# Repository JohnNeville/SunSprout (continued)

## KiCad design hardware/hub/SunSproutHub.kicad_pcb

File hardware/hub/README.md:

# SunSproutHub — KiCad project

The hub board's KiCad 10 project. Open `SunSproutHub.kicad_pro`.

For the design reasoning behind each IC and its passives, see [docs/hub/modules/](../../docs/hub/modules/).

## Layout

| Path | Contents |
|---|---|
| `SunSproutHub.kicad_sch` | Root/hierarchical top sheet |
| `sheets/` | Hierarchical sub-sheets (charger, fuel gauge, regulator, user I2C) |
| `SunSproutHub.kicad_pcb` | Board layout, hand-routed |
| `SunSproutHub.kicad_dru` | Custom design rules |
| `../libraries/` | Project-specific and vendored symbol/footprint libraries (shared with Satellite) |
| `spice_models/` | ngspice decks used to verify the reverse-polarity FETs |

## Board revisions

The revision is set by the `REV_NUM` text variable in `SunSproutHub.kicad_pro`, which the
silkscreen prints alongside the commit hash. Change the title block revision in the PCB to match.

| Change | Bump | Example |
|---|---|---|
| Fixes and part changes that keep the same ICs and board dimensions | Minor | 1.0 → 1.1 |
| A change that replaces the main ICs or changes the board dimensions | Major | 1.x → 2.0 |

All Rev 1.x boards share the same outline, mounting holes and connector positions, so the
documentation refers to them as Rev 1.x. Rev 1.0 is the first prototype, built from commit
`1645733`.

## What you can do without any extra setup

KiCad writes the full geometry of every symbol and footprint directly into the
`.kicad_sch` and `.kicad_pcb` files at placement time. The schematic and the board are
therefore self-contained. After cloning you can open both, run ERC and DRC, inspect every
part, and export gerbers and a pick-and-place file, with no libraries beyond the ones KiCad
ships with.

## External library dependencies

**3D models are not external.** The board file carries an embedded copy of every 3D model
(KiCad's "Collect and Embed 3D Models"), so the board renders completely with nothing
installed.

Footprints are mostly in-repo too. Three library entries still resolve outside it, and they
are only consulted when you update a footprint *from its library* — not to open, review,
render, or fabricate the board, because the geometry is already in the board file.

| Library | Resolves via | Parts |
|---|---|---|
| `Snapeda` | `KICAD_3RD_PARTY` | `J201`, `J202`, `U3`, `U8`, `U4`, `U5`, `U201`, `D5`, `U202`, `Q301`-`Q304` |
| `PCM_JLCPCB` | PCM package ([CDFER](https://github.com/CDFER/JLCPCB-Kicad-Library), MIT) | The 0402 capacitors |
| `PCM_SparkFun-Connector` | PCM package | The test points |
| `PCM_Capacitor_SMD_AKL` | PCM package | `C17` only, which is DNP and not fitted |

If KiCad reports these as missing, the board is still correct. To silence the warnings,
install the matching PCM packages and point `KICAD_3RD_PARTY` at your own third-party library
directory, or remove the unused entries from `fp-lib-table`.

The `USBC1` USB-C footprint and the `CN5` screw terminal are project footprints, in
`../libraries/footprints/project.pretty/`. The Espressif module's footprint and 3D model are
vendored under `../libraries/vendor/`.

### A note on licensing

Every library this design still depends on has stated terms: SnapEDA is CC BY-SA 4.0 with the
Design Exception 1.0, CDFER's library is MIT, and Espressif's is CC BY-SA 4.0. All three are
credited in [NOTICE.md](../../NOTICE.md). Earlier revisions used EasyEDA/LCSC content, whose
redistribution terms are not published; it has since been replaced throughout and no longer
appears in the design or the embedded model set.

## Regenerating the documentation assets

The board renders, schematic PDF, STEP model, interactive BOM, and pinout SVG under
`website/static/` are all build artifacts of the files here. Regenerate them from the
repository root after any schematic or layout change:

```bash
tools/generate-docs-assets.sh
```

Docker is the only prerequisite. No local KiCad installation is required.

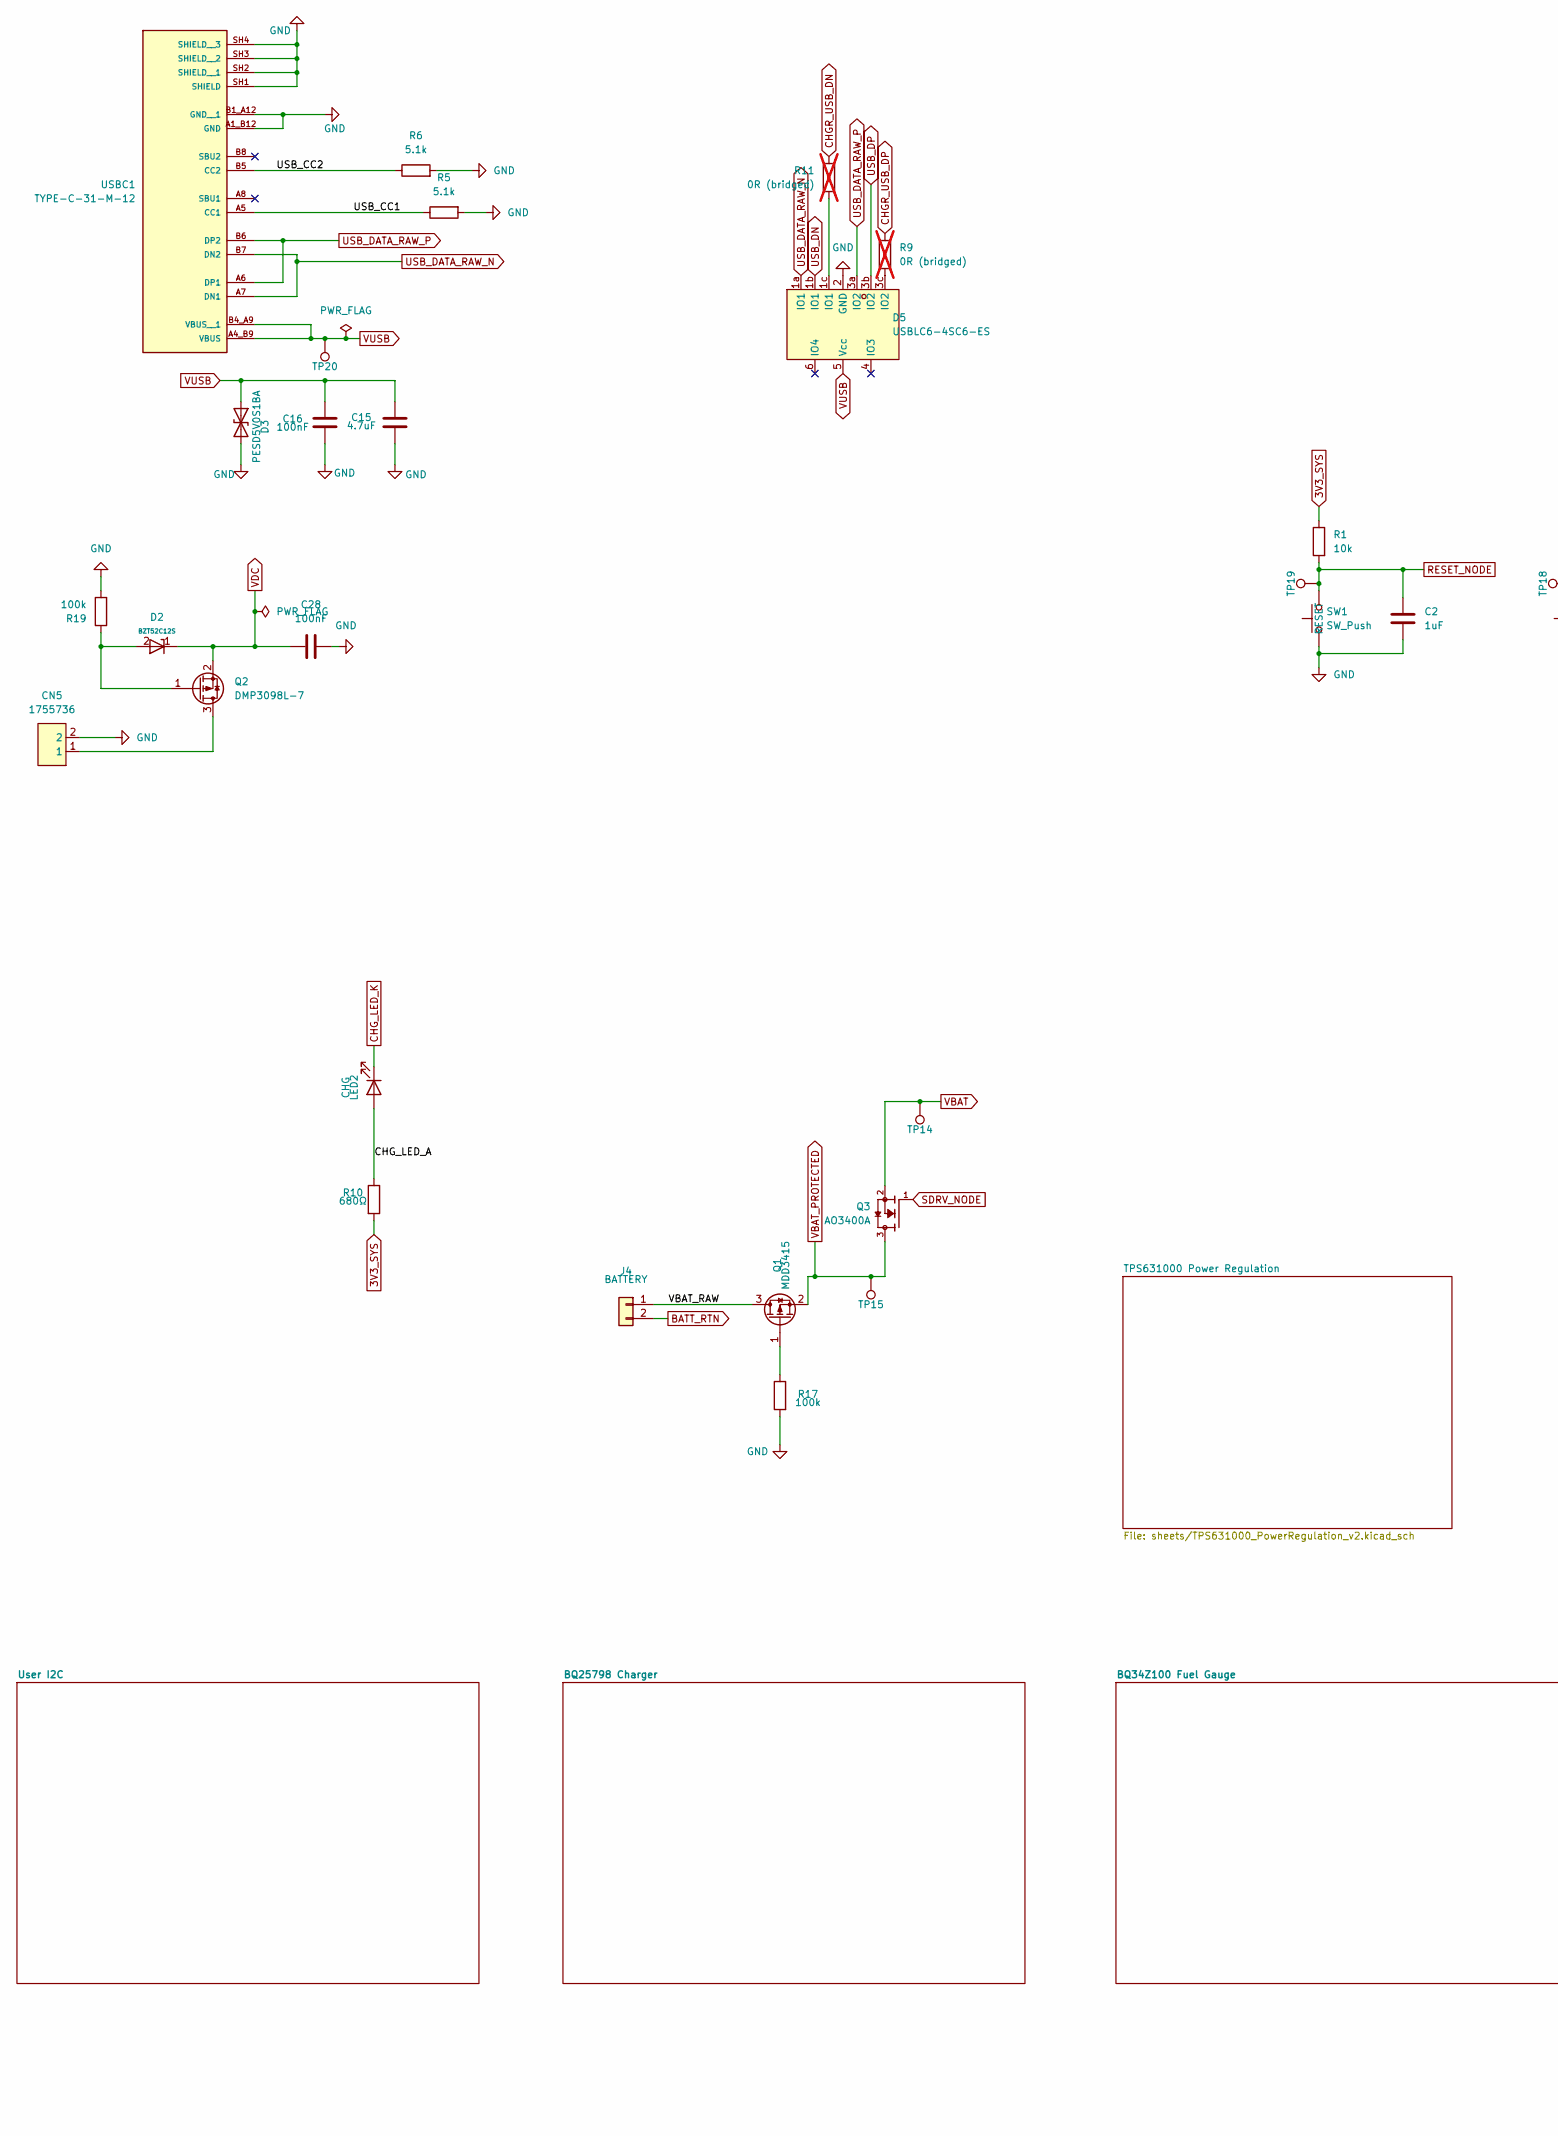
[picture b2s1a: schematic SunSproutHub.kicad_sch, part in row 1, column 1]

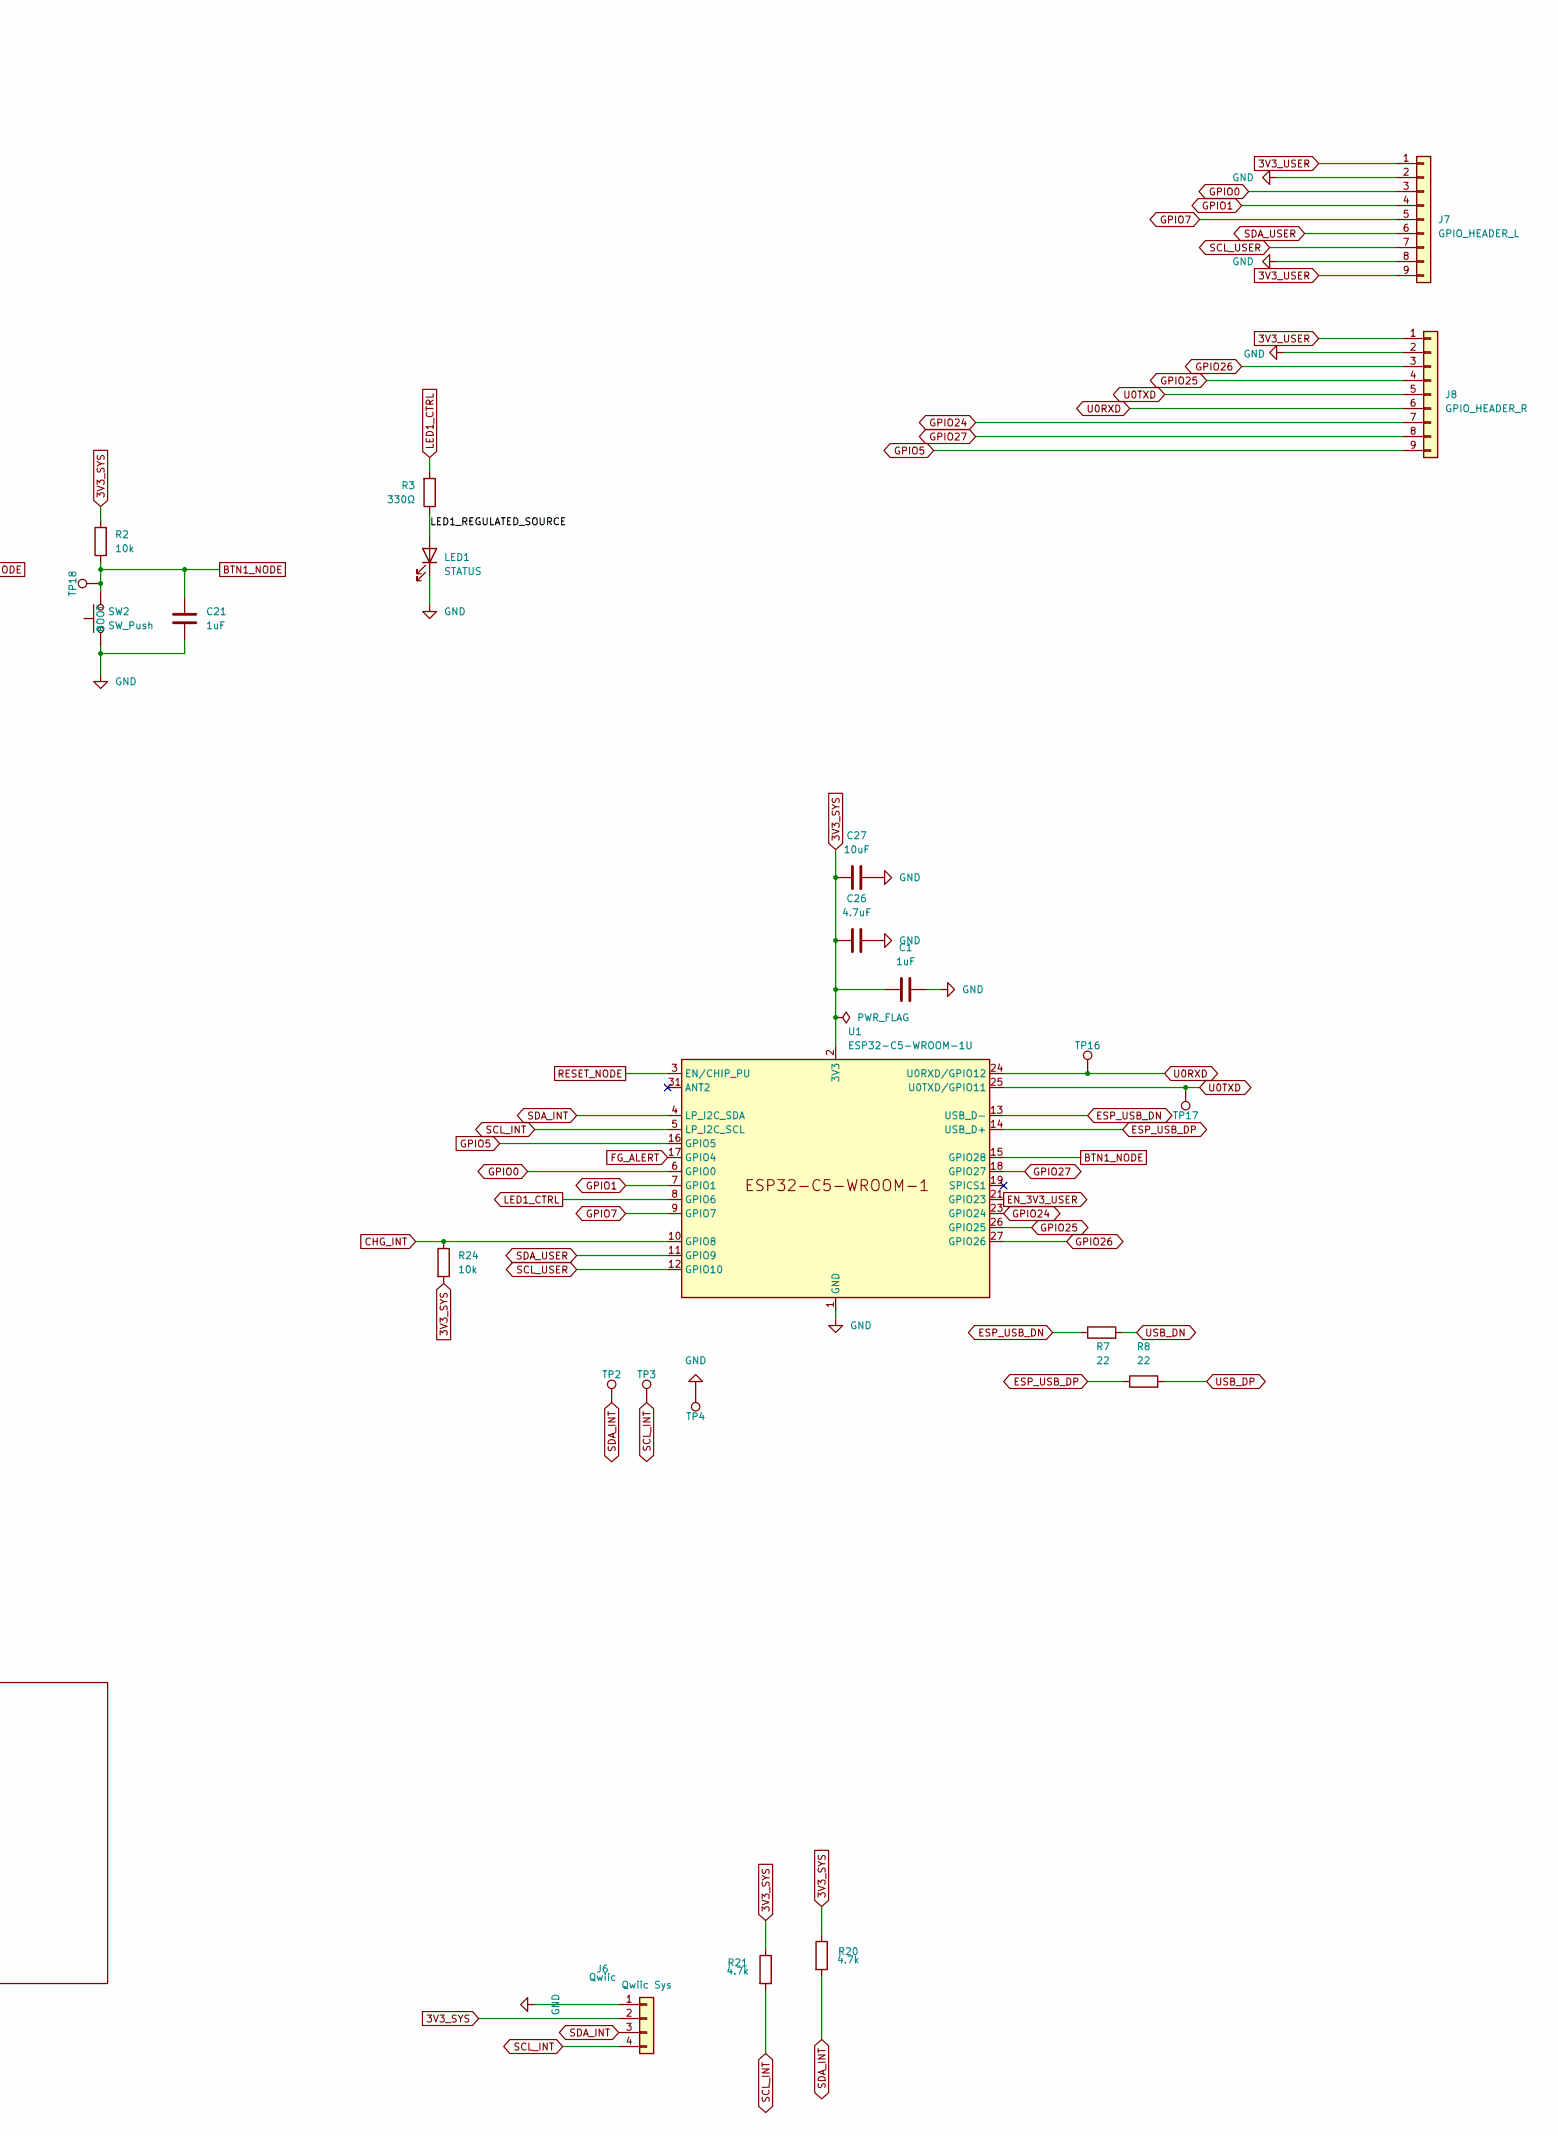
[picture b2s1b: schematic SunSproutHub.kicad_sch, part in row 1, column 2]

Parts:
C1, C2, C21: 1uF; C_0603_1608Metric; MPN CL10A105KB8NNNC; LCSC Part C15849
C15, C26: 4.7uF; C_0805_2012Metric; MPN CL21A475KAQNNNE; LCSC Part C1779
C16: 100nF; C_0402; MPN CL05B104KB54PNC; LCSC Part C307331
C27: 10uF; C_0603_1608Metric; MPN CL10A106MA8NRNC; LCSC Part C96446
C28: 100nF; C_0402; LCSC Part C307331
CN5: 1755736; DB125-2.54-2P-GN-S; MPN DB125-2.54-2P-GN-S; LCSC Part C918120
D2: BZT52C12S; D_SOD-323; MPN BZT52C12S; LCSC Part C19077447
D3: PESD5V0S1BA; D_SOD-523; LCSC Part C20615818
D5: USBLC6-4SC6-ES; USBLC6-4SC6-ES_WIthNetTie; MPN USBLC6-4SC6-ES; LCSC Part C5180279
J4: BATTERY; JST_PH_S2B-PH-K_1x02_P2.00mm_Horizontal; MPN S2B-PH-K(LF)(SN); LCSC Part C265016
J6: Qwiic; JST_SH_BM04B-SRSS-TB_1x04-1MP_P1.00mm_Vertical; MPN BM04B-SRSS-TB(LF)(SN); LCSC Part C160390
J7: GPIO_HEADER_L; LeftSide_PinHeader_1x09_P2.54mm_Vertical
J8: GPIO_HEADER_R; PinHeader_1x09_P2.54mm_Vertical
LED1: STATUS; LED_0603_1608Metric; MPN KT-0603W; LCSC Part C2290
LED2: CHG; LED_0603_1608Metric; MPN KT-0603R; LCSC Part C2286
Q1: MDD3415; SOT-23; MPN MDD3415; LCSC Part C840839
Q2: DMP3098L-7; SOT-23; MPN DMP3098L-7; LCSC Part C150492
Q3: AO3400A; SOT95P280X125-3N; MPN AO3400A; LCSC Part C20917
R1, R2, R24: 10k; R_0603_1608Metric; MPN 0603WAF1002T5E; LCSC Part C25804
R3: 330Ω; R_0603_1608Metric; MPN 0603WAF3300T5E; LCSC Part C23138
R5, R6: 5.1k; R_0603_1608Metric; MPN 0603WAF5101T5E; LCSC Part C23186
R7, R8: 22; R_0603_1608Metric; MPN 0603WAF220JT5E; LCSC Part C23345
R9, R11: 0R (bridged); R_0603_1608Metric; not fitted
R10: 680Ω; R_0603_1608Metric; MPN 0603WAF6800T5E; LCSC Part C23228
R17, R19: 100k; R_0603_1608Metric; MPN 0603WAF1003T5E; LCSC Part C25803
R20, R21: 4.7k; R_0603_1608Metric; MPN 0603WAF4701T5E; LCSC Part C23162
SW1, SW2: SW_Push; SW_SPST_TS-1088-xR020; MPN TS-1088-AR02016; LCSC Part C720477
TP2: SDA_INT; TestPoint-1.0mm
TP3: SCL_INT; TestPoint-1.0mm
TP4: GND; TestPoint-1.0mm
TP14: VBAT; TestPoint-1.0mm
TP15: VBAT_PRO; TestPoint-1.0mm
TP16: U0RXD; TestPoint-1.0mm
TP17: U0TXD; TestPoint-1.0mm
TP18: BOOT; TestPoint-1.0mm
TP19: RESET; TestPoint-1.0mm
TP20: VUSB; TestPoint-1.0mm
U1: ESP32-C5-WROOM-1U; MPN ESP32-C5-WROOM-1U-N8R8-V1.2; LCSC Part C54951858
USBC1: TYPE-C-31-M-12; USB-C_TYPE-C-31-M-12; MPN TYPE-C-31-M-12; LCSC Part C165948

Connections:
3V3_SYS: C1.1, C26.1, C27.1, J6.2 (3v3), R1.1, R2.2, R10.2, R20.1, R21.1, R24.2, U1.2 (3V3); also elsewhere on the board
3V3_USER: J7.1, J7.9, J8.1; also elsewhere on the board
/CHG_LED_A: LED2.2 (A), R10.1
/LED1_REGULATED_SOURCE: LED1.2 (A), R3.1
/USB_CC1: R5.1, USBC1.A5 (CC1)
/USB_CC2: R6.1, USBC1.B5 (CC2)
/VBAT_RAW: J4.1, Q1.3 (D)
BATT_RTN: J4.2; also elsewhere on the board
BTN1_NODE: C21.1, R2.1, SW2.1, TP18.1 (1_1), U1.15 (GPIO28)
CHGR_USB_DN: R11.1; also elsewhere on the board
CHGR_USB_DP: R9.1; also elsewhere on the board
CHG_INT: R24.1, U1.10 (GPIO8); also elsewhere on the board
CHG_LED_K: LED2.1 (K); also elsewhere on the board
EN_3V3_USER: U1.21 (GPIO23); also elsewhere on the board
ESP_USB_DN: R7.1, U1.13 (USB_D-)
ESP_USB_DP: R8.1, U1.14 (USB_D+)
FG_ALERT: U1.17 (GPIO4); also elsewhere on the board
GND: C1.2, C2.2, C15.2, C16.2, C21.2, C26.2, C27.2, C28.2, CN5.2, D3.2 (A2), D5.2 (GND), J6.1 (GND), J7.2, J7.8, J8.2, LED1.1 (K), R5.2, R6.2, R17.2, R19.2, SW1.2, SW2.2, TP4.1 (1_1), U1.1 (GND), U1.28 (GND), U1.29 (GND), U1.30 (GND), U1.32 (GND), USBC1.A1_B12 (GND), USBC1.B1_A12 (GND__1), USBC1.SH1 (SHIELD), USBC1.SH2 (SHIELD__1), USBC1.SH3 (SHIELD__2), USBC1.SH4 (SHIELD__3); also elsewhere on the board
GPIO0: J7.3, U1.6 (GPIO0)
GPIO1: J7.4, U1.7 (GPIO1)
GPIO5: J8.9, U1.16 (GPIO5)
GPIO7: J7.5, U1.9 (GPIO7)
GPIO24: J8.7, U1.23 (GPIO24)
GPIO25: J8.4, U1.26 (GPIO25)
GPIO26: J8.3, U1.27 (GPIO26)
GPIO27: J8.8, U1.18 (GPIO27)
LED1_CTRL: R3.2, U1.8 (GPIO6)
unnamed: D5.1c (IO1), R11.2
unnamed: D5.3c (IO2), R9.2
unnamed: Q1.1 (G), R17.1
unnamed: CN5.1, Q2.3 (D)
unnamed: D2.2, Q2.1 (G), R19.1
RESET_NODE: C2.1, R1.2, SW1.1, TP19.1 (1_1), U1.3 (EN/CHIP_PU)
SCL_INT: J6.4 (SCL), R21.2, TP3.1 (1_1), U1.5 (LP_I2C_SCL); also elsewhere on the board
SCL_USER: J7.7, U1.12 (GPIO10); also elsewhere on the board
SDA_INT: J6.3 (SDA), R20.2, TP2.1 (1_1), U1.4 (LP_I2C_SDA); also elsewhere on the board
SDA_USER: J7.6, U1.11 (GPIO9); also elsewhere on the board
SDRV_NODE: Q3.1; also elsewhere on the board
U0RXD: J8.6, TP16.1 (1_1), U1.24 (U0RXD/GPIO12)
U0TXD: J8.5, TP17.1 (1_1), U1.25 (U0TXD/GPIO11)
USB_DATA_RAW_N: D5.1a (IO1), USBC1.A7 (DN1), USBC1.B7 (DN2)
USB_DATA_RAW_P: D5.3a (IO2), USBC1.A6 (DP1), USBC1.B6 (DP2)
USB_DN: D5.1b (IO1), R7.2
USB_DP: D5.3b (IO2), R8.2
VBAT: Q3.2, TP14.1 (1_1); also elsewhere on the board
VBAT_PROTECTED: Q1.2 (S), Q3.3, TP15.1 (1_1); also elsewhere on the board
VDC: C28.1, D2.1, Q2.2 (S); also elsewhere on the board
VUSB: C15.1, C16.1, D3.1 (A1), D5.5 (Vcc), TP20.1 (1_1), USBC1.A4_B9 (VBUS), USBC1.B4_A9 (VBUS__1); also elsewhere on the board

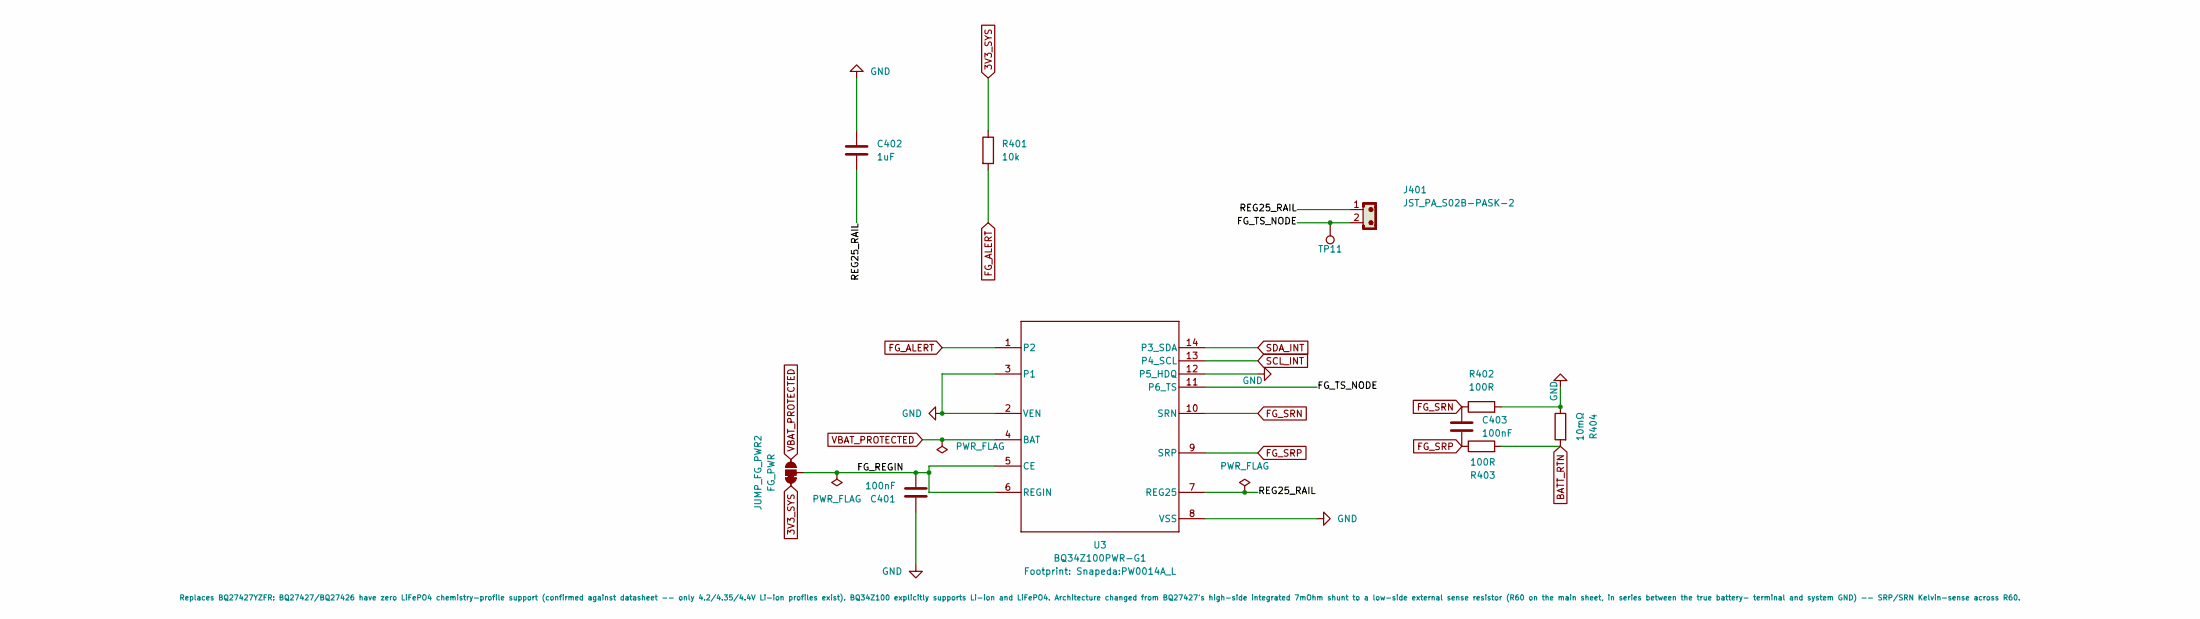
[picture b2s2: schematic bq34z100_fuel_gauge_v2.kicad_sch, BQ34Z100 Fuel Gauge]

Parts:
C401, C403: 100nF; C_0402; MPN CL05B104KB54PNC; LCSC Part C307331
C402: 1uF; C_0603_1608Metric; MPN CL10A105KB8NNNC; LCSC Part C15849
J401: JST_PA_S02B-PASK-2; JST_PA_S02B-PASK-2_1x02_P2.00mm_Horizontal; MPN S02B-PASK-2(LF)(SN); LCSC Part C265094
JUMP_FG_PWR2: FG_PWR; SolderJumper-3_P1.3mm_Bridged12_RoundedPad1.0x1.5mm_NumberL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
R401: 10k; R_0603_1608Metric; MPN 0603WAF1002T5E; LCSC Part C25804
R402, R403: 100R; R_0603_1608Metric; MPN 0603WAF1000T5E; LCSC Part C22775
R404: 10mΩ; R_1206_3216Metric; LCSC Part C105362
TP11: FG_TS_NODE; TestPoint-1.0mm
U3: BQ34Z100PWR-G1; PW0014A_L; MPN BQ34Z100PWR-G1; LCSC Part C91302

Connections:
3V3_SYS: JUMP_FG_PWR2.1 (A), R401.1; also elsewhere on the board
/BQ34Z100 Fuel Gauge/FG_REGIN: C401.2, JUMP_FG_PWR2.2 (B), U3.5 (CE), U3.6 (REGIN)
/BQ34Z100 Fuel Gauge/FG_TS_NODE: J401.2, TP11.1 (1_1), U3.11 (P6_TS)
/BQ34Z100 Fuel Gauge/REG25_RAIL: C402.2, J401.1, U3.7 (REG25)
BATT_RTN: R403.2, R404.2; also elsewhere on the board
FG_ALERT: R401.2, U3.1 (P2); also elsewhere on the board
FG_SRN: C403.1, R402.1, U3.10 (SRN)
FG_SRP: C403.2, R403.1, U3.9 (SRP)
GND: C401.1, C402.1, R402.2, R404.1, U3.2 (VEN), U3.3 (P1), U3.8 (VSS), U3.12 (P5_HDQ); also elsewhere on the board
SCL_INT: U3.13 (P4_SCL); also elsewhere on the board
SDA_INT: U3.14 (P3_SDA); also elsewhere on the board
VBAT_PROTECTED: JUMP_FG_PWR2.3 (C), U3.4 (BAT); also elsewhere on the board

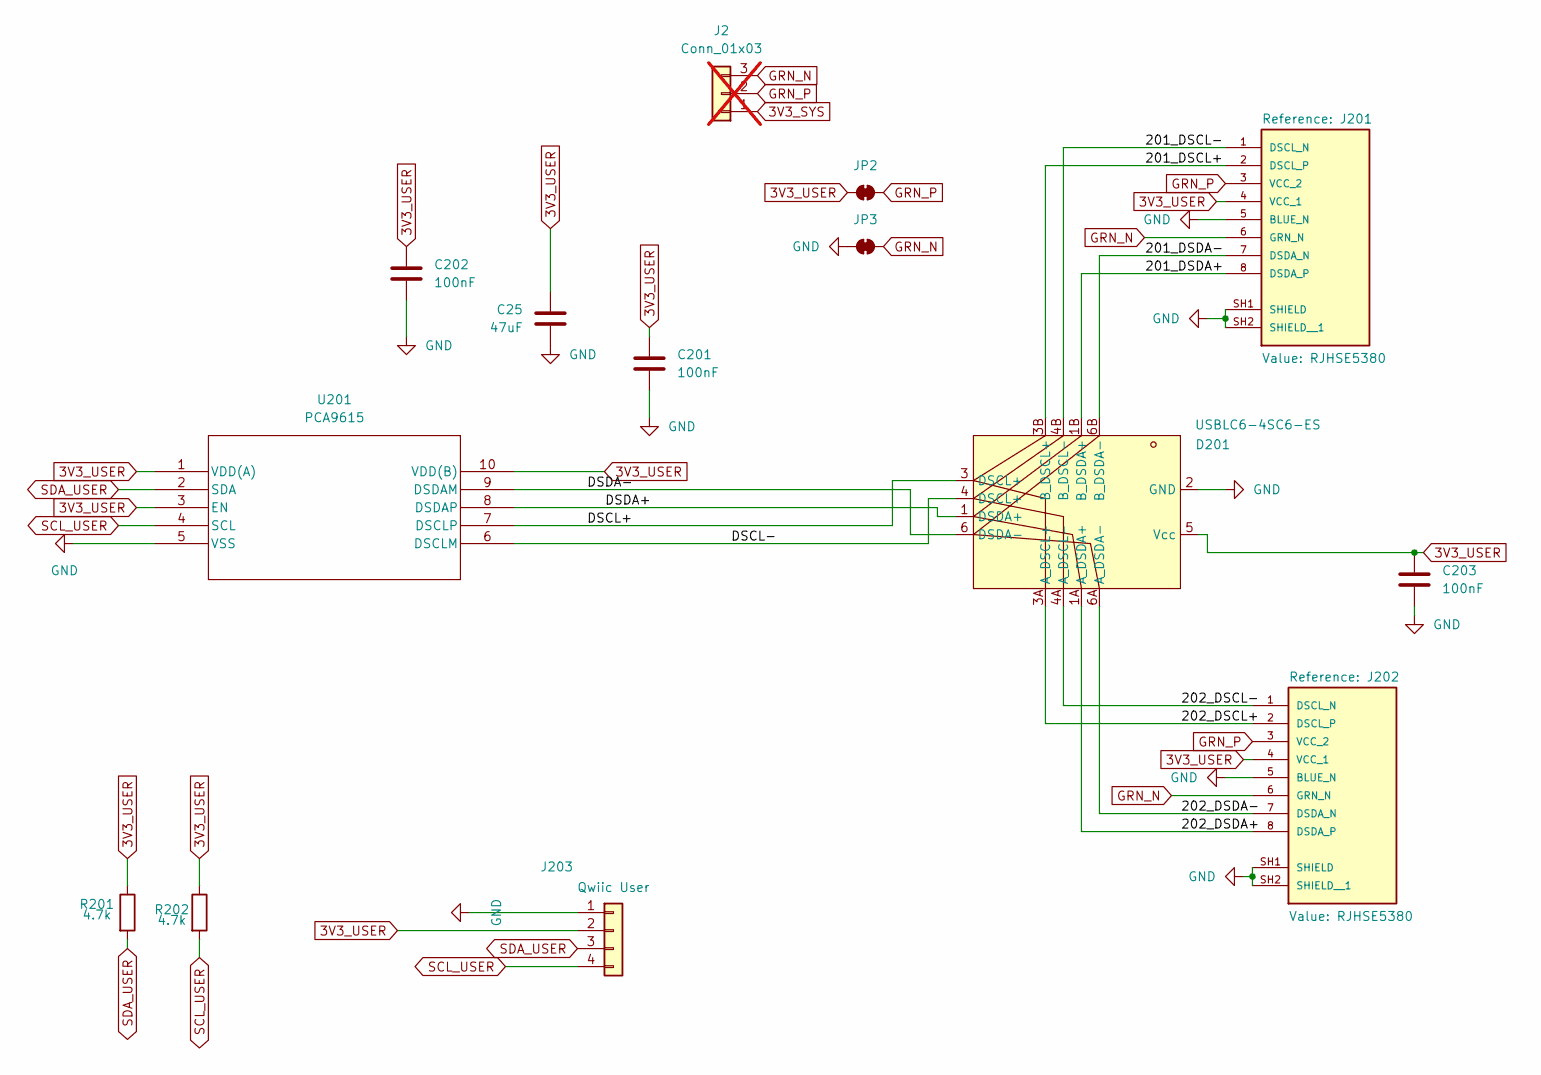
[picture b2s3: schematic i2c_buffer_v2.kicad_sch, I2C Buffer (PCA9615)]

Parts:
C25: 47uF; C_0805_2012Metric; LCSC Part C16780
C201, C202: 100nF; C_0402; MPN CL05B104KB54PNC; LCSC Part C307331
C203: 100nF; C_0402; LCSC Part C307331
D201: USBLC6-4SC6-ES; SOT23-6L_STM_w_NetTies_1346ab; MPN USBLC6-4SC6-ES; LCSC Part C5180279
J2: Conn_01x03; PinHeader_1x03_P2.54mm_Vertical; not fitted
J201, J202: RJHSE5380; AMPHENOL_RJHSE5380; MPN RJHSE5380; LCSC Part C464586
J203: Qwiic; JST_SH_BM04B-SRSS-TB_1x04-1MP_P1.00mm_Vertical; MPN BM04B-SRSS-TB(LF)(SN); LCSC Part C160390
JP2, JP3: SolderJumper-2_P1.3mm_Bridged_RoundedPad1.0x1.5mm
R201, R202: 4.7k; R_0603_1608Metric; MPN 0603WAF4701T5E; LCSC Part C23162
U201: PCA9615; TSSOP10_SOT552-1_NXP-L; MPN PCA9615DPZ; LCSC Part C3824272

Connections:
3V3_SYS: J2.1; also elsewhere on the board
3V3_USER: C25.1, C201.1, C202.1, C203.1, D201.5 (Vcc), J201.4 (VCC_1), J202.4 (VCC_1), J203.2 (3v3), JP2.1 (A), R201.1, R202.1, U201.1 (VDD(A)), U201.3 (EN), U201.10 (VDD(B)); also elsewhere on the board
/User I2C/201_DSCL+: D201.3B (B_DSCL+), J201.2 (DSCL_P)
/User I2C/201_DSCL-: D201.4B (B_DSCL-), J201.1 (DSCL_N)
/User I2C/201_DSDA+: D201.1B (B_DSDA+), J201.8 (DSDA_P)
/User I2C/201_DSDA-: D201.6B (B_DSDA-), J201.7 (DSDA_N)
/User I2C/202_DSCL+: D201.3A (A_DSCL+), J202.2 (DSCL_P)
/User I2C/202_DSCL-: D201.4A (A_DSCL-), J202.1 (DSCL_N)
/User I2C/202_DSDA+: D201.1A (A_DSDA+), J202.8 (DSDA_P)
/User I2C/202_DSDA-: D201.6A (A_DSDA-), J202.7 (DSDA_N)
/User I2C/DSCL+: D201.3 (DSCL+), U201.7 (DSCLP)
/User I2C/DSCL-: D201.4 (DSCL+), U201.6 (DSCLM)
/User I2C/DSDA+: D201.1 (DSDA+), U201.8 (DSDAP)
/User I2C/DSDA-: D201.6 (DSDA-), U201.9 (DSDAM)
GND: C25.2, C201.2, C202.2, C203.2, D201.2 (GND), J201.5 (BLUE_N), J201.SH1 (SHIELD), J201.SH2 (SHIELD__1), J202.5 (BLUE_N), J202.SH1 (SHIELD), J202.SH2 (SHIELD__1), J203.1 (GND), JP3.1 (A), U201.5 (VSS); also elsewhere on the board
GRN_N: J2.3, J201.6 (GRN_N), J202.6 (GRN_N), JP3.2 (B)
GRN_P: J2.2, J201.3 (VCC_2), J202.3 (VCC_2), JP2.2 (B)
SCL_USER: J203.4 (SCL), R202.2, U201.4 (SCL); also elsewhere on the board
SDA_USER: J203.3 (SDA), R201.2, U201.2 (SDA); also elsewhere on the board

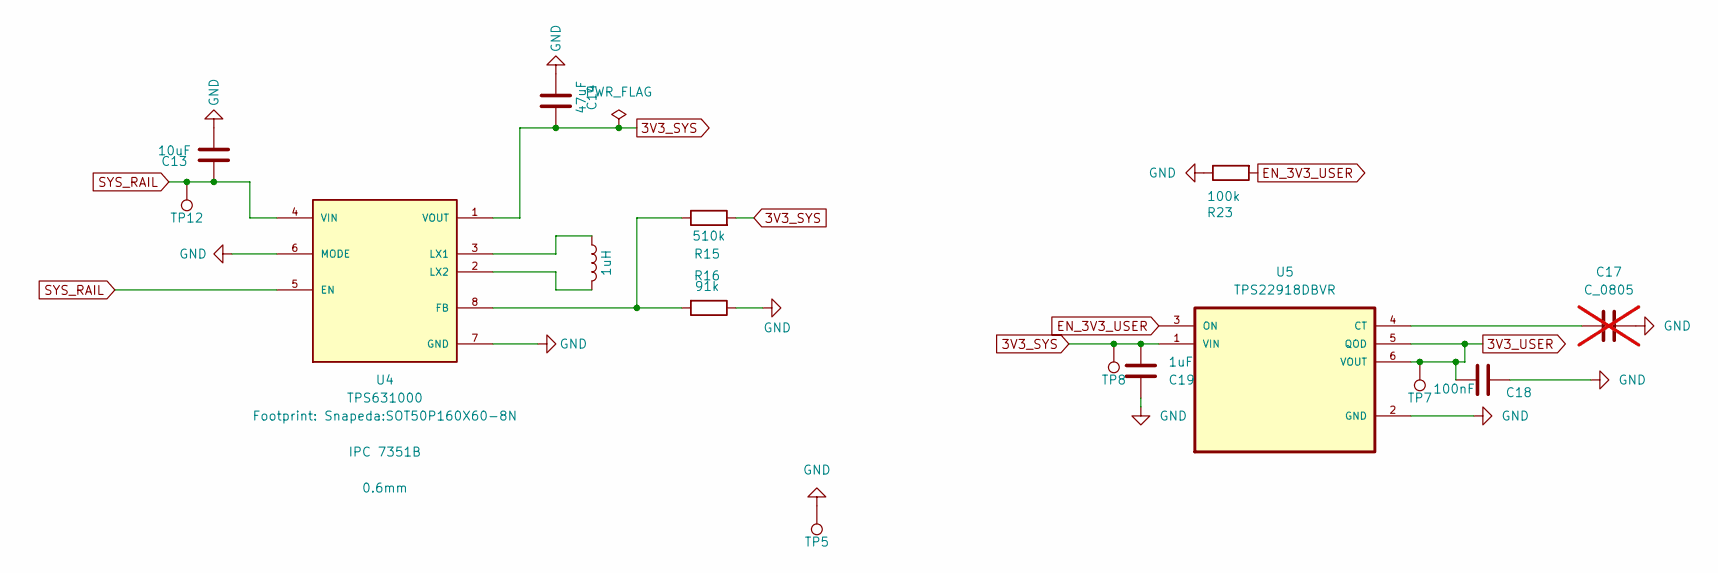
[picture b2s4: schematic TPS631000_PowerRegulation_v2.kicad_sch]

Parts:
C13: 10uF; C_0603_1608Metric; MPN CL10A106MA8NRNC; LCSC Part C96446
C14: 47uF; C_0805_2012Metric; LCSC Part C16780
C17: C_0805; C_0805_2012Metric; not fitted
C18: 100nF; C_0402; LCSC Part C307331
C19: 1uF; C_0603_1608Metric; MPN CL10A105KB8NNNC; LCSC Part C15849
L2: 1uH; L_Changjiang_FTC252012S; MPN FTC252012S1R0MBCD; LCSC Part C22400405
R15: 510k; R_0603_1608Metric; LCSC Part C23192
R16: 91k; R_0603_1608Metric; LCSC Part C23265
R23: 100k; R_0603_1608Metric; MPN 0603WAF1003T5E; LCSC Part C25803
TP5: GND; TestPoint-1.0mm
TP7: 3V3_USER; TestPoint-1.0mm
TP8: 3V3_SYS; TestPoint-1.0mm
TP12: SYS_RAIL; TestPoint-1.0mm
U4: TPS631000; SOT50P160X60-8N; MPN TPS631000DRLR; LCSC Part C5219190
U5: TPS22918DBVR; SOT95P280X145-6N; MPN TPS22918DBVR; LCSC Part C131941

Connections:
3V3_SYS: C14.1, C19.1, R15.2, TP8.1 (1_1), U4.1 (VOUT), U5.1 (VIN); also elsewhere on the board
3V3_USER: C18.2, TP7.1 (1_1), U5.5 (QOD), U5.6 (VOUT); also elsewhere on the board
EN_3V3_USER: R23.2, U5.3 (ON); also elsewhere on the board
GND: C13.2, C14.2, C17.2, C18.1, C19.2, R16.1, R23.1, TP5.1 (1_1), U4.6 (MODE), U4.7 (GND), U5.2 (GND); also elsewhere on the board
unnamed: R15.1, R16.2, U4.8 (FB)
unnamed: L2.2, U4.3 (LX1)
unnamed: L2.1, U4.2 (LX2)
unnamed: C17.1, U5.4 (CT)
SYS_RAIL: C13.1, TP12.1 (1_1), U4.4 (VIN), U4.5 (EN); also elsewhere on the board
